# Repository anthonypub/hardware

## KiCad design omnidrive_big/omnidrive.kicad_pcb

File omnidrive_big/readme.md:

List of components for digikey at https://www.digikey.com/en/mylists/list/VGMZK5BE5X

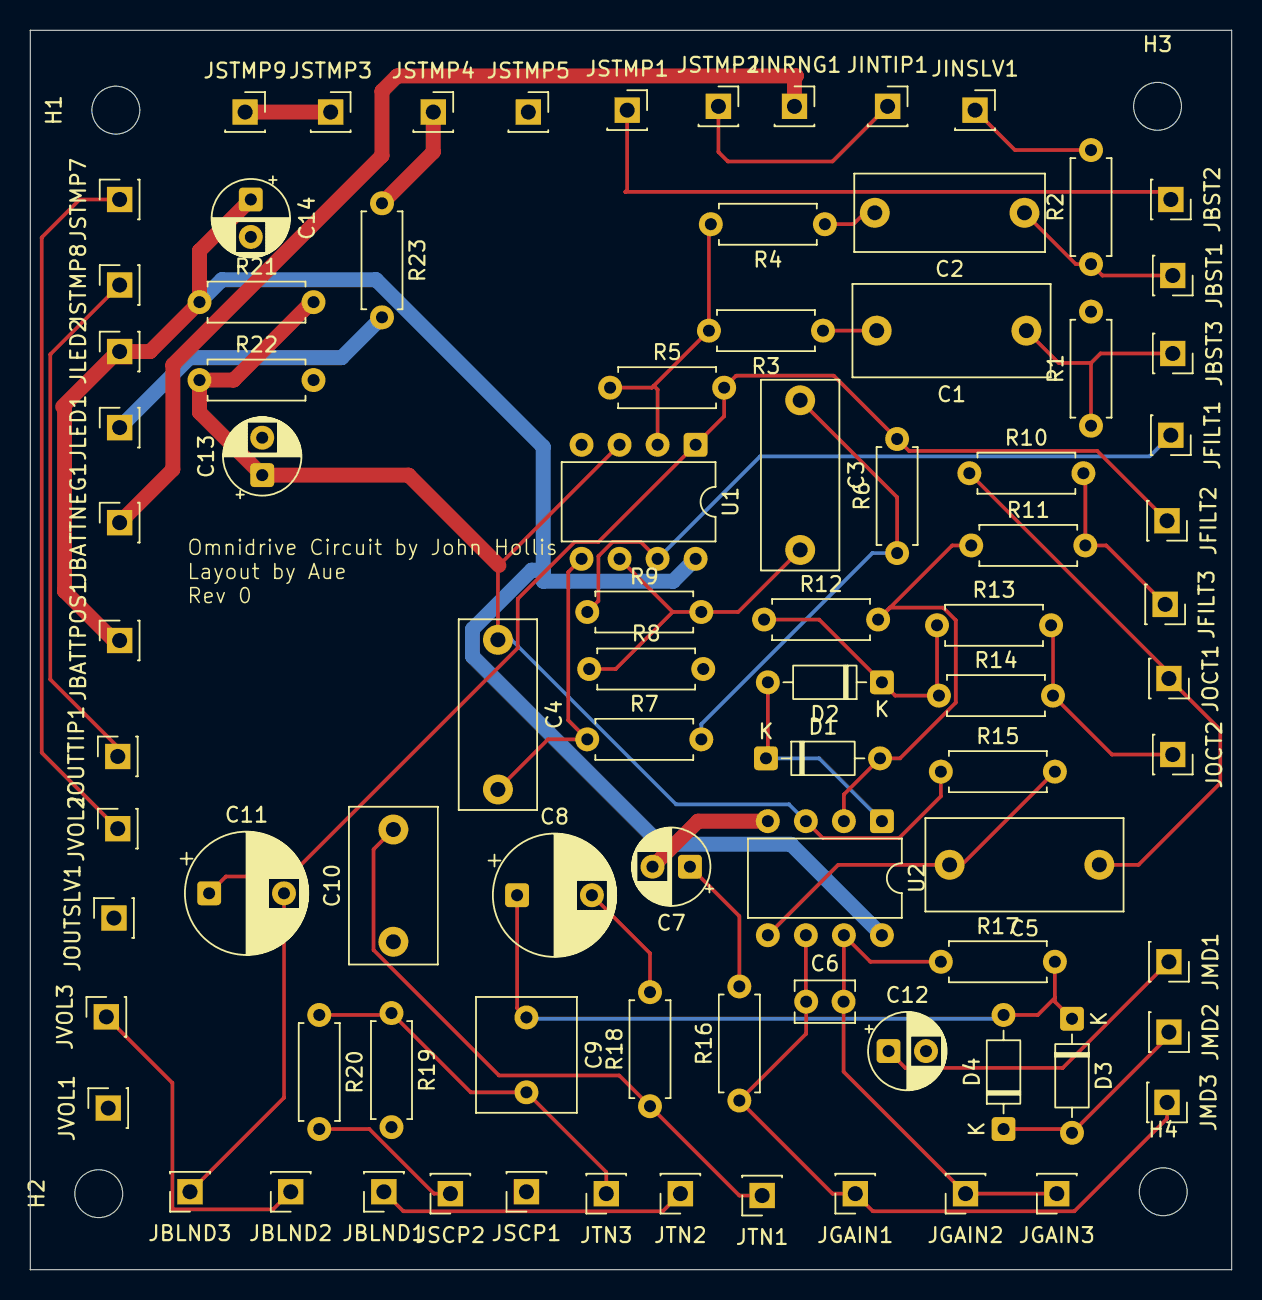
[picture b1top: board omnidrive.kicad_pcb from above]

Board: 2 copper layers, 80.3 x 82.8 mm, 89 parts (0 on the bottom side), 41 nets.

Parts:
C1, C5: 0.01uF; C_Rect_L13.0mm_W6.0mm_P10.00mm_FKS3_FKP3_MKS4
C2, C3, C4: 0.001uF; C_Disc_D12.5mm_W5.0mm_P10.00mm
C6: 47pF; C_Disc_D3.8mm_W2.6mm_P2.50mm
C7, C12, C13, C14: 10uF; CP_Radial_D5.0mm_P2.50mm
C8, C11: 1uF; CP_Radial_D8.0mm_P5.00mm
C9: 0.047uF; C_Rect_L7.5mm_W6.5mm_P5.00mm
C10: 0.1uF; C_Rect_L10.3mm_W5.7mm_P7.50mm_MKS4
D1, D2, D3, D4: 1N914; D_DO-35_SOD27_P7.62mm_Horizontal
H1, H2, H3, H4: MountingHole; MountingHole_3.2mm_M3
JBATTNEG1: Conn_01x01_Pin; PinSocket_1x01_P2.54mm_Vertical
JBATTPOS1: Conn_01x01_Pin; PinSocket_1x01_P2.54mm_Vertical
JBLND1, JBLND2, JBLND3: Conn_01x01_Pin; PinSocket_1x01_P2.54mm_Vertical
JBST1, JBST2, JBST3: Conn_01x01_Pin; PinSocket_1x01_P2.54mm_Vertical
JFILT1, JFILT2, JFILT3: Conn_01x01_Pin; PinSocket_1x01_P2.54mm_Vertical
JGAIN1, JGAIN2, JGAIN3: Conn_01x01_Pin; PinSocket_1x01_P2.54mm_Vertical
JINRNG1: Conn_01x01_Pin; PinSocket_1x01_P2.54mm_Vertical
JINSLV1: Conn_01x01_Pin; PinSocket_1x01_P2.54mm_Vertical
JINTIP1: Conn_01x01_Pin; PinSocket_1x01_P2.54mm_Vertical
JLED1, JLED2: Conn_01x01_Pin; PinSocket_1x01_P2.54mm_Vertical
JMD1, JMD2, JMD3: Conn_01x01_Pin; PinSocket_1x01_P2.54mm_Vertical
JOCT1, JOCT2: Conn_01x01_Pin; PinSocket_1x01_P2.54mm_Vertical
JOUTSLV1: Conn_01x01_Pin; PinSocket_1x01_P2.54mm_Vertical
JOUTTIP1: Conn_01x01_Pin; PinSocket_1x01_P2.54mm_Vertical
JSCP1, JSCP2: Conn_01x01_Pin; PinSocket_1x01_P2.54mm_Vertical
JSTMP1, JSTMP2, JSTMP3, JSTMP4, JSTMP5, JSTMP7, JSTMP8, JSTMP9: Conn_01x01_Pin; PinSocket_1x01_P2.54mm_Vertical
JTN1, JTN2, JTN3: Conn_01x01_Pin; PinSocket_1x01_P2.54mm_Vertical
JVOL1, JVOL2, JVOL3: Conn_01x01_Pin; PinSocket_1x01_P2.54mm_Vertical
R1, R2: 10M; R_Axial_DIN0207_L6.3mm_D2.5mm_P7.62mm_Horizontal
R3: 330K; R_Axial_DIN0207_L6.3mm_D2.5mm_P7.62mm_Horizontal
R4, R8, R9, R15: 100K; R_Axial_DIN0207_L6.3mm_D2.5mm_P7.62mm_Horizontal
R5: 1M; R_Axial_DIN0207_L6.3mm_D2.5mm_P7.62mm_Horizontal
R6, R7: 220K; R_Axial_DIN0207_L6.3mm_D2.5mm_P7.62mm_Horizontal
R10, R11, R12, R13, R14, R19, R21, R22, R23: 10K; R_Axial_DIN0207_L6.3mm_D2.5mm_P7.62mm_Horizontal
R16, R17, R20: 1K; R_Axial_DIN0207_L6.3mm_D2.5mm_P7.62mm_Horizontal
R18: 3.9K; R_Axial_DIN0207_L6.3mm_D2.5mm_P7.62mm_Horizontal
U1, U2: TL072; DIP-8_W7.62mm

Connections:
+9V: C14.1, JBATTPOS1.1 (Pin_1_1), JLED2.1 (Pin_1_1), R21.1, U1.8 (V+), U2.8 (V+)
/EFFECT_OUT: JSTMP7.1 (Pin_1_1), JVOL2.1 (Pin_1_1)
/Vb: C4.1, C13.1, R15.1, R21.2, R22.1, U1.3 (+), U2.3 (+)
GND: C7.2, C10.1, C12.2, C13.2, C14.2, JINSLV1.1 (Pin_1_1), JOUTSLV1.1 (Pin_1_1), JSCP1.1 (Pin_1_1), JSTMP5.1 (Pin_1_1), JVOL1.1 (Pin_1_1), R1.2, R2.2, R8.2, R19.2, R22.2, U1.4 (V-), U2.4 (V-)
unnamed: C1.2, R3.1
unnamed: C2.2, R4.1
unnamed: C3.1, R6.1, R7.2
unnamed: C7.1, R16.2
unnamed: C8.2, R18.2
unnamed: D1.2 (A), R11.1, R12.2, U2.2 (-)
unnamed: D1.1 (K), D2.2 (A), U2.1
unnamed: D2.1 (K), R12.1, R13.1, R14.1
unnamed: D3.2 (A), D4.1 (K), JMD2.1 (Pin_1_1)
unnamed: C8.1, C9.1, D3.1 (K), D4.2 (A), R17.2
unnamed: JBATTNEG1.1 (Pin_1_1), JINRNG1.1 (Pin_1_1)
unnamed: JBLND1.1 (Pin_1_1), JTN2.1 (Pin_1_1)
unnamed: JBLND2.1 (Pin_1_1), JVOL3.1 (Pin_1_1)
unnamed: C11.2, JBLND3.1 (Pin_1_1)
unnamed: C2.1, JBST1.1 (Pin_1_1), R2.1
unnamed: JBST2.1 (Pin_1_1), JSTMP1.1 (Pin_1_1)
unnamed: C1.1, JBST3.1 (Pin_1_1), R1.1
unnamed: JFILT1.1 (Pin_1_1), R9.1, U1.7
unnamed: C11.1, JFILT2.1 (Pin_1_1), R5.2, R6.2, U1.1
unnamed: JFILT3.1 (Pin_1_1), R10.2, R11.2
unnamed: C6.1, JGAIN1.1 (Pin_1_1), JMD3.1 (Pin_1_1), R16.1, U2.6 (-)
unnamed: C6.2, JGAIN2.1 (Pin_1_1), JGAIN3.1 (Pin_1_1), R17.1, U2.7
unnamed: JINTIP1.1 (Pin_1_1), JSTMP2.1 (Pin_1_1)
unnamed: JLED1.1 (Pin_1_1), R23.2
unnamed: C12.1, JMD1.1 (Pin_1_1)
unnamed: C5.1, JOCT1.1 (Pin_1_1), R10.1
unnamed: JOCT2.1 (Pin_1_1), R13.2, R14.2
unnamed: JOUTTIP1.1 (Pin_1_1), JSTMP8.1 (Pin_1_1)
unnamed: JSCP2.1 (Pin_1_1), R20.2
unnamed: JSTMP3.1 (Pin_1_1), JSTMP9.1 (Pin_1_1)
unnamed: JSTMP4.1 (Pin_1_1), R23.1
unnamed: C10.2, JTN1.1 (Pin_1_1), R18.1
unnamed: C9.2, JTN3.1 (Pin_1_1), R19.1, R20.1
unnamed: R3.2, R4.2, R5.1, U1.2 (-)
unnamed: C4.2, R7.1, U1.5 (+)
unnamed: C3.2, R8.1, R9.2, U1.6 (-)
unnamed: C5.2, R15.2, U2.5 (+)

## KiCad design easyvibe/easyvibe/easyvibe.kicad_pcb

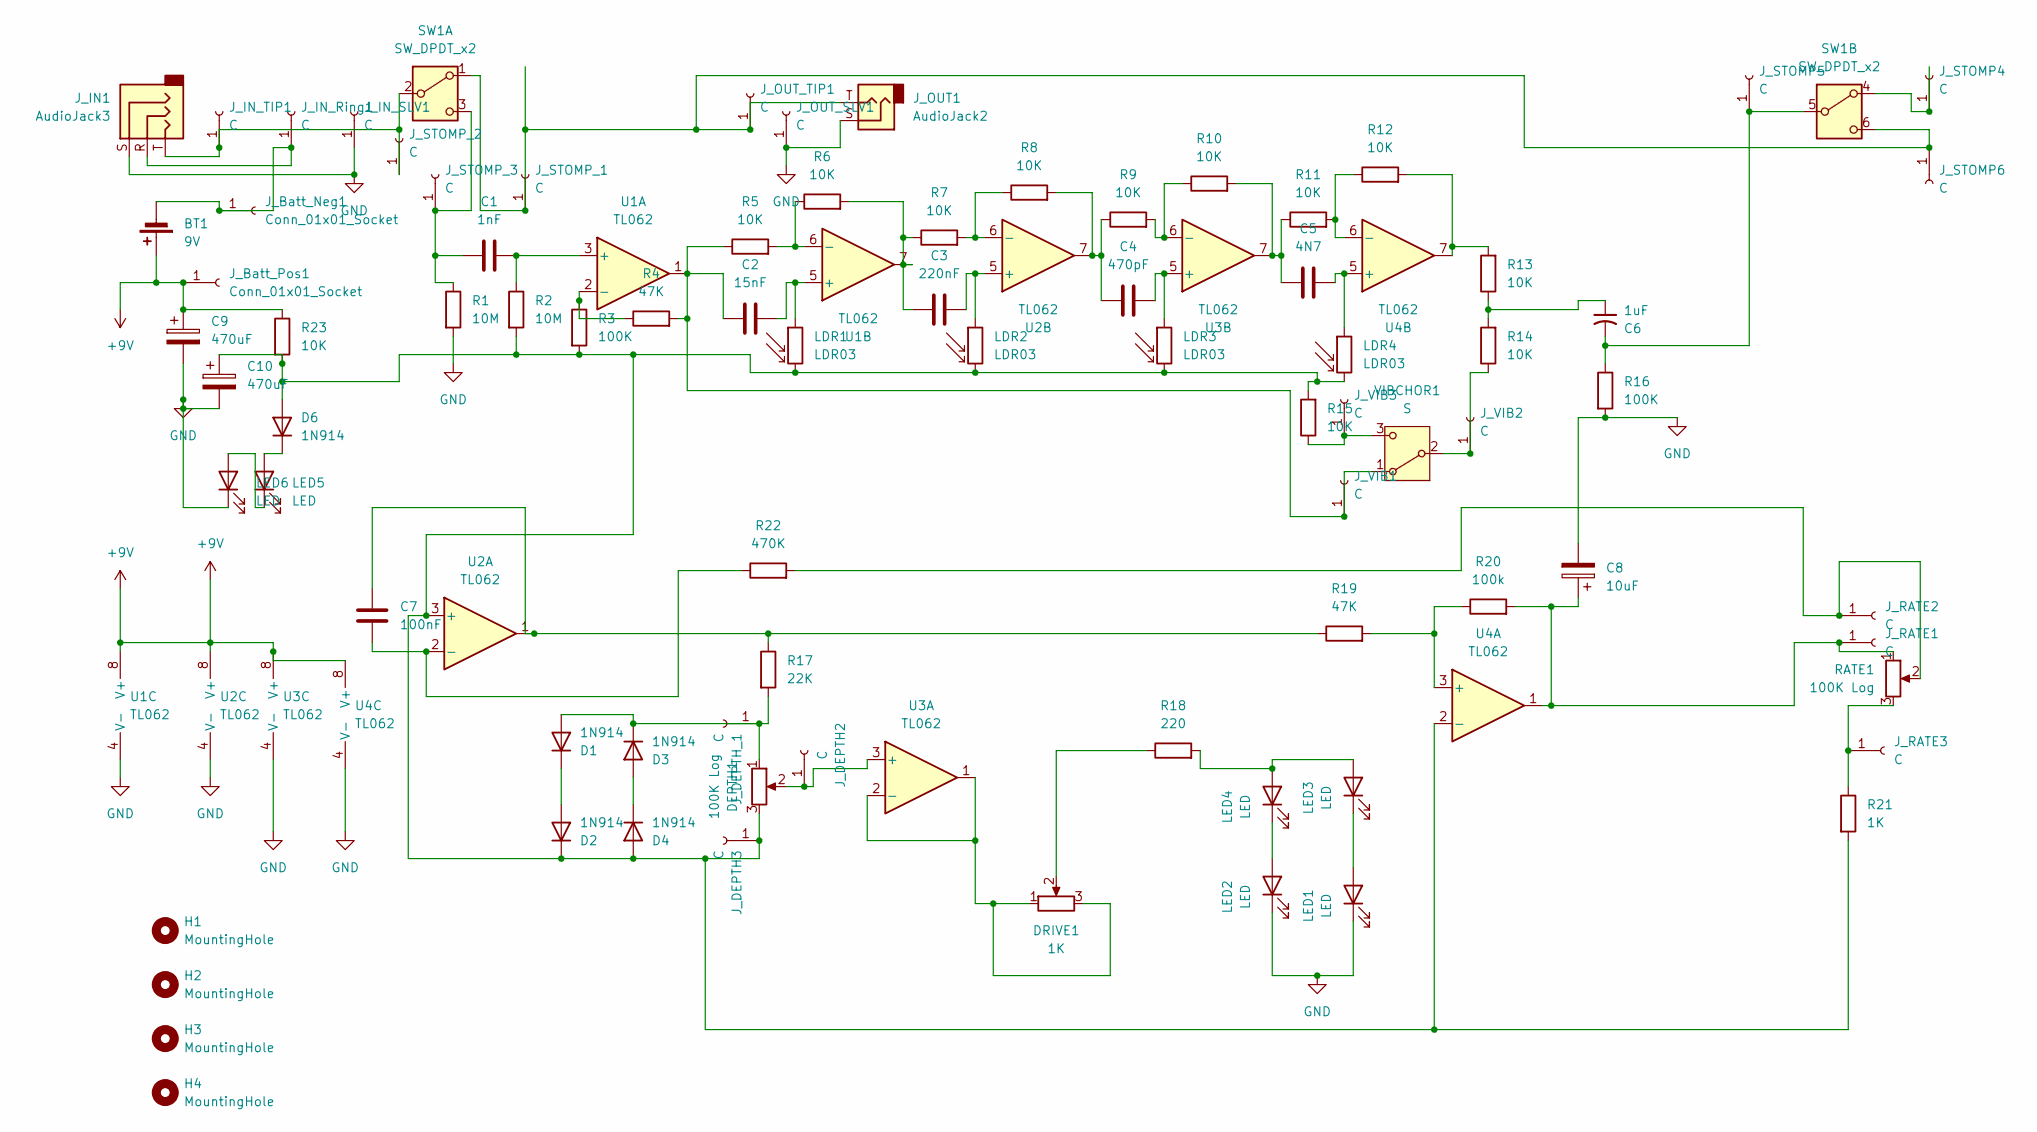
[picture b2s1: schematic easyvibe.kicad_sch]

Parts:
BT1: 9V
C1: 1nF; C_Rect_L7.2mm_W2.5mm_P5.00mm_FKS2_FKP2_MKS2_MKP2
C2: 15nF; C_Rect_L7.2mm_W2.5mm_P5.00mm_FKS2_FKP2_MKS2_MKP2
C3: 220nF; C_Rect_L7.2mm_W2.5mm_P5.00mm_FKS2_FKP2_MKS2_MKP2
C4: 470pF; C_Rect_L7.2mm_W4.5mm_P5.00mm_FKS2_FKP2_MKS2_MKP2
C5: 4N7; C_Rect_L7.2mm_W2.5mm_P5.00mm_FKS2_FKP2_MKS2_MKP2
C6: 1uF; C_Radial_D5.0mm_H5.0mm_P2.00mm
C7: 100nF; C_Rect_L7.2mm_W2.5mm_P5.00mm_FKS2_FKP2_MKS2_MKP2
C8: 10uF; CP_Radial_D5.0mm_P2.00mm
C9, C10: 470uF; CP_Radial_D8.0mm_P3.50mm
D1, D2, D3, D4, D6: 1N914; AFL-W2C8.9D
DEPTH1: 100K Log
DRIVE1: 1K; Potentiometer_Runtron_RM-063_Horizontal
H1, H2, H3, H4: MountingHole; MountingHole_3.2mm_M3
J_Batt_Neg1: Conn_01x01_Socket; PinSocket_1x01_P2.54mm_Vertical
J_Batt_Pos1: Conn_01x01_Socket; PinSocket_1x01_P2.54mm_Vertical
J_DEPTH2, J_DEPTH3: C; PinSocket_1x01_P2.54mm_Vertical
J_DEPTH_1: C; PinSocket_1x01_P2.54mm_Vertical
J_IN1: AudioJack3
J_IN_Ring1: C; PinSocket_1x01_P2.54mm_Vertical
J_IN_SLV1: C; PinSocket_1x01_P2.54mm_Vertical
J_IN_TIP1: C; PinSocket_1x01_P2.54mm_Vertical
J_OUT1: AudioJack2
J_OUT_SLV1: C; PinSocket_1x01_P2.54mm_Vertical
J_OUT_TIP1: C; PinSocket_1x01_P2.54mm_Vertical
J_RATE1, J_RATE2, J_RATE3: C; PinSocket_1x01_P2.54mm_Vertical
J_STOMP4, J_STOMP5, J_STOMP6: C; PinSocket_1x01_P2.54mm_Vertical
J_STOMP_1, J_STOMP_2, J_STOMP_3: C; PinSocket_1x01_P2.54mm_Vertical
J_VIB1, J_VIB2, J_VIB3: C; PinSocket_1x01_P2.54mm_Vertical
LDR1, LDR2, LDR3, LDR4: LDR03; TO_NSL_19M_ADP
LED1, LED2, LED3, LED4, LED5, LED6: LED; T-100_4P8X3P15_ONS
R1, R2: 10M; R_Axial_DIN0207_L6.3mm_D2.5mm_P7.62mm_Horizontal
R3, R16: 100K; RES_LR1_TYCO_TYC
R4, R19: 47K; RES_LR1_TYCO_TYC
R5, R6, R7, R8, R9, R10, R11, R12, R13, R14, R15, R23: 10K; YAG_MF25_YAG
R17: 22K; RES_LR1_TYCO_TYC
R18: 220; RES_LR1_TYCO_TYC
R20: 100k; RES_LR1_TYCO_TYC
R21: 1K; RES_LR1_TYCO_TYC
R22: 470K; RES_LR1_TYCO_TYC
RATE1: 100K Log
SW1: SW_DPDT_x2
U1, U2, U3, U4: TL062; DIP-8_W7.62mm
VIBCHOR1: S

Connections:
+9V: BT1.1 (+), C9.1, J_Batt_Pos1.1 (Pin_1_1), R23.1, U1.8 (V+), U2.8 (V+), U3.8 (V+), U4.8 (V+)
GND: C8.2, C9.2, C10.2, J_IN1.S, J_IN_SLV1.1 (Pin_1_1), J_OUT1.S, J_OUT_SLV1.1 (Pin_1_1), LED1.1 (K), LED2.1 (K), LED6.1 (K), R1.2, R16.2, U1.4 (V-), U2.4 (V-), U3.4 (V-), U4.4 (V-)
unnamed: C3.1, R6.2, R7.1, U1.7
unnamed: C4.1, R8.2, R9.1, U2.7
unnamed: C5.1, R10.2, R11.1, U3.7
unnamed: C6.1, R13.1, R14.2
unnamed: C7.1, R17.1, R19.1, U2.1
unnamed: D1.2 (A), D3.1 (K), DEPTH1.1, J_DEPTH_1.1 (Pin_1_1), R17.2
unnamed: D1.1 (K), D2.2 (A)
unnamed: C10.1, D2.1 (K), D4.2 (A), D6.2 (A), DEPTH1.3, J_DEPTH3.1 (Pin_1_1), LDR1.2, LDR2.2, LDR3.2, LDR4.2, R2.2, R3.2, R15.2, R21.2, R23.2, U2.3 (+), U4.2 (-)
unnamed: D3.2 (A), D4.1 (K)
unnamed: D6.1 (K), LED5.2 (A)
unnamed: DRIVE1.2, R18.1
unnamed: BT1.2 (-), J_Batt_Neg1.1 (Pin_1_1), J_IN1.R, J_IN_Ring1.1 (Pin_1_1)
unnamed: DEPTH1.2, J_DEPTH2.1 (Pin_1_1), U3.3 (+)
unnamed: J_IN1.T, J_IN_TIP1.1 (Pin_1_1), J_STOMP_2.1 (Pin_1_1), SW1.2 (B)
unnamed: C8.1, J_RATE1.1 (Pin_1_1), R20.2, RATE1.1, U4.1
unnamed: J_RATE2.1 (Pin_1_1), R22.2, RATE1.2
unnamed: J_RATE3.1 (Pin_1_1), R21.1, RATE1.3
unnamed: C6.2, J_STOMP5.1 (Pin_1_1), R16.1, SW1.5 (B)
unnamed: C1.1, J_STOMP_3.1 (Pin_1_1), R1.1, SW1.3 (C)
unnamed: C2.1, J_VIB1.1 (Pin_1_1), R4.2, R5.1, U1.1, VIBCHOR1.1 (A)
unnamed: J_VIB2.1 (Pin_1_1), R14.1, VIBCHOR1.2 (B)
unnamed: J_VIB3.1 (Pin_1_1), R15.1, VIBCHOR1.3 (C)
unnamed: LED1.2 (A), LED3.1 (K)
unnamed: LED2.2 (A), LED4.1 (K)
unnamed: LED3.2 (A), LED4.2 (A), R18.2
unnamed: LED5.1 (K), LED6.2 (A)
unnamed: R12.2, R13.2, U4.7
unnamed: C1.2, R2.1, U1.3 (+)
unnamed: R3.1, R4.1, U1.2 (-)
unnamed: C2.2, LDR1.1, U1.5 (+)
unnamed: R5.2, R6.1, U1.6 (-)
unnamed: C7.2, R22.1, U2.2 (-)
unnamed: C3.2, LDR2.1, U2.5 (+)
unnamed: R7.2, R8.1, U2.6 (-)
unnamed: DRIVE1.1, DRIVE1.3, U3.1, U3.2 (-)
unnamed: C4.2, LDR3.1, U3.5 (+)
unnamed: R9.2, R10.1, U3.6 (-)
unnamed: R19.2, R20.1, U4.3 (+)
unnamed: C5.2, LDR4.1, U4.5 (+)
unnamed: R11.2, R12.1, U4.6 (-)

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
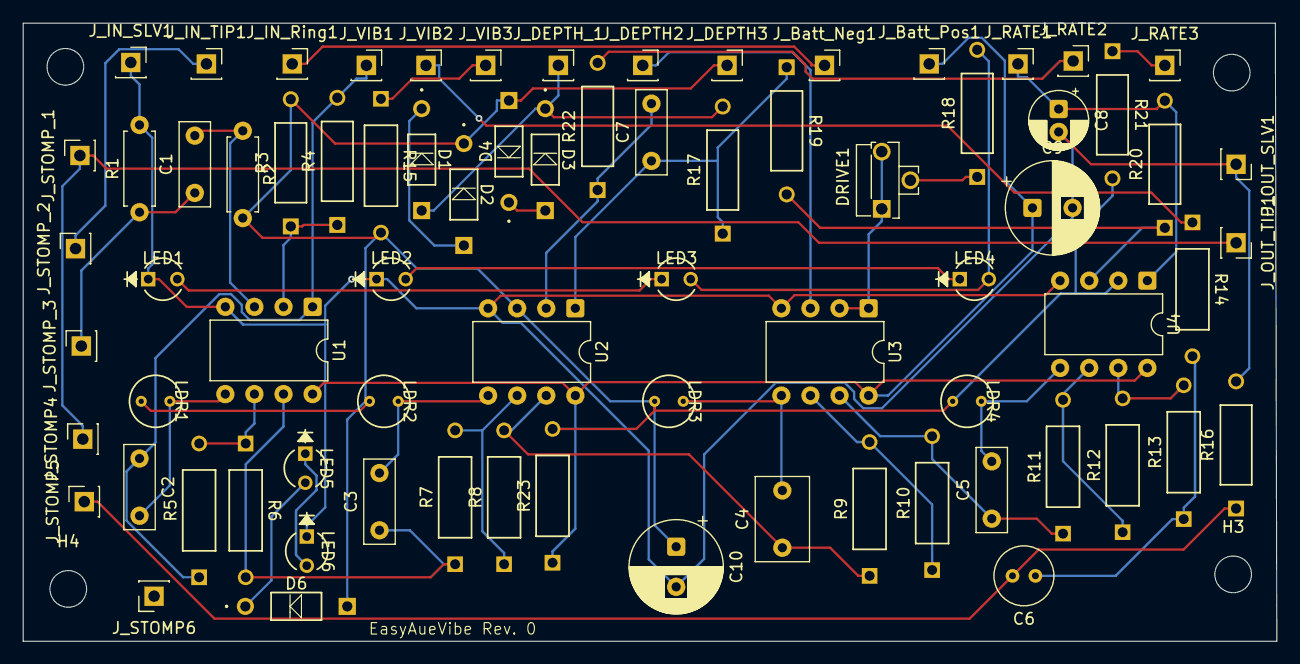
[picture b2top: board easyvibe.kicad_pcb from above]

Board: 2 copper layers, 109.5 x 54.0 mm, 79 parts (0 on the bottom side), 43 nets.

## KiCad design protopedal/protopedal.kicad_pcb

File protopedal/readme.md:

Idea: A helper PCB for pedal construction, similar to many that have been done.

Will include:

- Power from regular pedal wart + 9V, with auto-switch
- Optional Polarity protection?
- Option for reverse polarity (for the weird transistors)
- Input and output jacks
- 3PDT switching
- LED for power
- LED for effect
- Common Pots? Would be nice to have pre-mounted pots in common sizes to avoid having to solder
    Protis mini includes 1k, 10k, 100k, 1M. I've seen 500Ks to so add those?
- A few switches as well, SPST and SPDT.
    
- Output pins for:
    - Power + Gnd (multiple, more for ground)
    - Direct access to all jack pins
    - Jack pins through switch
    - Optional half-voltage rail

Some resources:
https://learn.sparkfun.com/tutorials/proto-pedal-assembly-and-theory-guide/all (Includes pointers to reverse polarity safety)

Optional: 5v in case I want to do microcontroller stuff.

Very optional: Protis guys have a cool take that plugs directly into a normal breadboard. 

Foot switch wiring: https://madbeanpedals.com/tutorials/downloads/MBP_FootswitchWiring.pdf

List is here:
https://www.digikey.com/en/mylists/list/RVMUHCSVVZ

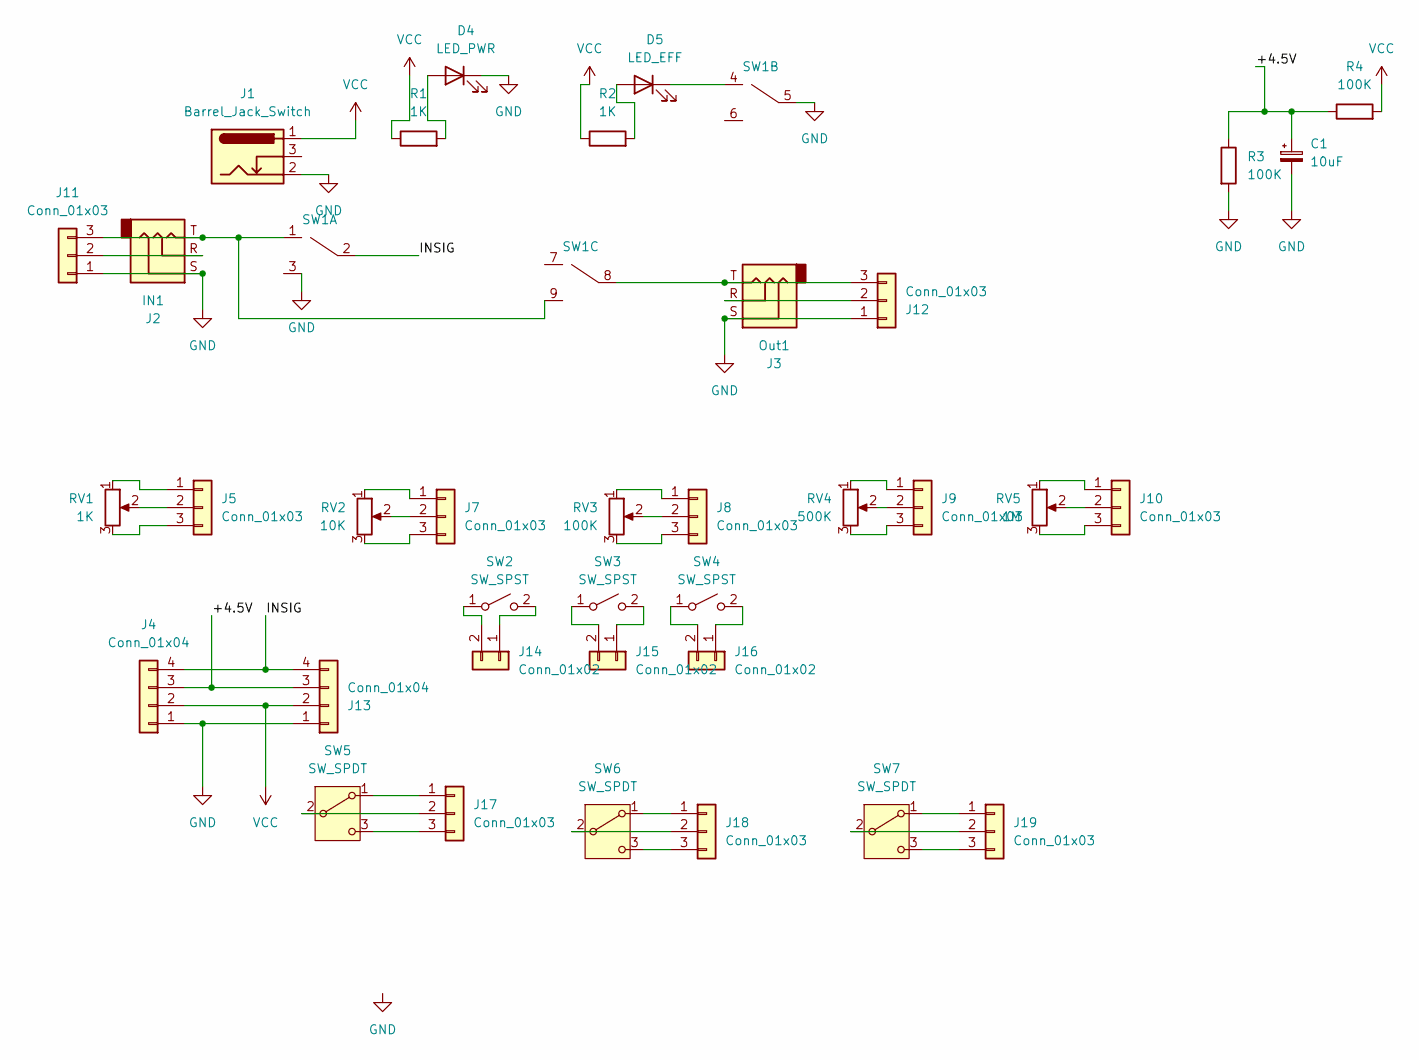
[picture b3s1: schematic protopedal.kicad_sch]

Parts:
C1: 10uF; CP_Radial_D5.0mm_P2.00mm
D4: LED_PWR; LED_D5.0mm
D5: LED_EFF; LED_D5.0mm
J1: Barrel_Jack_Switch; PRT-10811_SPK
J2: IN1; CONN_MHDR_AMP
J3: Out1; CONN_MHDR_AMP
J4, J13: Conn_01x04; PinHeader_1x04_P2.54mm_Vertical
J5, J7, J8, J9, J10, J11, J12, J17, J18, J19: Conn_01x03; PinHeader_1x03_P2.54mm_Vertical
J14, J15, J16: Conn_01x02; PinHeader_1x02_P2.54mm_Vertical
R1, R2: 1K; STA_CF14_STP
R3, R4: 100K; STA_CF14_STP
RV1: 1K; TRIM_PT01-D115D-B104
RV2: 10K; TRIM_PT01-D115D-B104
RV3: 100K; TRIM_PT01-D115D-B104
RV4: 500K; TO_3310Y
RV5: 1M; TO_3310Y
SW1: STOMP-SWITCH-3PDT
SW2, SW3, SW4: SW_SPST; SW2_GF-123-0054_CWI
SW5, SW6, SW7: SW_SPDT; ASE1E-2M-10-Z_NDC

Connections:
/+4.5V: C1.1, J4.3, J13.3, R3.1, R4.1
/INSIG: J4.4, J13.4, SW1.2
GND: C1.2, D4.1 (K), J1.2, J2.S, J3.S, J4.1, J11.1, J12.1, J13.1, R3.2, SW1.5
unnamed: D4.2 (A), R1.2
unnamed: D5.2 (A), R2.2
unnamed: D5.1 (K), SW1.4
unnamed: J5.1, RV1.1
unnamed: J5.2, RV1.2
unnamed: J5.3, RV1.3
unnamed: J7.1, RV2.1
unnamed: J7.2, RV2.2
unnamed: J7.3, RV2.3
unnamed: J8.1, RV3.1
unnamed: J8.2, RV3.2
unnamed: J8.3, RV3.3
unnamed: J9.1, RV4.1
unnamed: J9.2, RV4.2
unnamed: J9.3, RV4.3
unnamed: J10.1, RV5.1
unnamed: J10.2, RV5.2
unnamed: J10.3, RV5.3
unnamed: J2.R, J11.2
unnamed: J2.T, J11.3, SW1.1, SW1.9
unnamed: J3.R, J12.2
unnamed: J3.T, J12.3, SW1.8
unnamed: J14.1, SW2.2 (B)
unnamed: J14.2, SW2.1 (A)
unnamed: J15.1, SW3.2 (B)
unnamed: J15.2, SW3.1 (A)
unnamed: J16.1, SW4.2 (B)
unnamed: J16.2, SW4.1 (A)
unnamed: J17.1, SW5.1 (A)
unnamed: J17.2, SW5.2 (B)
unnamed: J17.3, SW5.3 (C)
unnamed: J18.1, SW6.1 (A)
unnamed: J18.2, SW6.2 (B)
unnamed: J18.3, SW6.3 (C)
unnamed: J19.1, SW7.1 (A)
unnamed: J19.2, SW7.2 (B)
unnamed: J19.3, SW7.3 (C)
VCC: J1.1, J4.2, J13.2, R1.1, R2.1, R4.2

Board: 2 copper layers, 37 parts (0 on the bottom side), 41 nets, no tracks yet.

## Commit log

2026-05-16 big omnidrive
2026-05-16 Latest updates
2026-05-17 got import from digikey models working
2026-05-17 all footprints
2026-05-17 Added board cuts and mounting holes
2026-05-17 add ground fill on edge
2026-05-17 initial component placement everywheres
2026-05-17 some fixes
2026-05-17 fix ground fill
2026-05-20 more tweaks, make board slightly smaller to fit box
2026-05-21 readme for proto
2026-05-21 add easyvibe parts list
2026-05-21 begin of protopedal
2026-05-21 Add symbols for pin headers
2026-05-21 fixed some stuff
2026-05-22 started wiring
2026-05-23 more
2026-05-28 Added text
2026-05-30 autorouted version sent to oshpark
2026-05-31 Fix omnidrive schematic; other things too
2026-06-15 copy before fixing errors after build
2026-06-15 Fix switch wiring
2026-06-18 my own layout, components placed
2026-06-18 placed + routed everything except ground plane
2026-06-20 fix checks
2026-06-20 fixed unconnected pin
